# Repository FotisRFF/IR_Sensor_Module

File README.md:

# IR_Sensor_Module

An optimized, production-ready infrared sensor module designed for precision obstacle detection, edge sensing, or line tracking. This repository contains the complete PCB design files created in **KiCad**, including manufacturing panelization layouts and single-board configurations.

---

## Key Hardware Features

* **Compact Footprint:** Engineered for tight spaces with surface-mount components and clean trace routing.
* **Optimized Optics:** Integrated phototransistor and IR LED arrangement designed for reliable ambient light rejection and consistent response distances.
* **Panelization Ready:** Includes optimized panel layouts suitable for automated pick-and-place assembly and batch fabrication.

---

## Board Layouts & Visualizations

### Panel View

* **PCB Layout:**  

* **3D Rendering:**  

---

### Single Board View

* **PCB Layout:**  

* **3D Rendering:**  

---

## Repository Structure

```text
├── Kicad_Files/          # Schematic & PCB layout project files
├── Fabrication/          # Gerber files, panel assembly drawings, and BOM
└── README.md             # Project documentation

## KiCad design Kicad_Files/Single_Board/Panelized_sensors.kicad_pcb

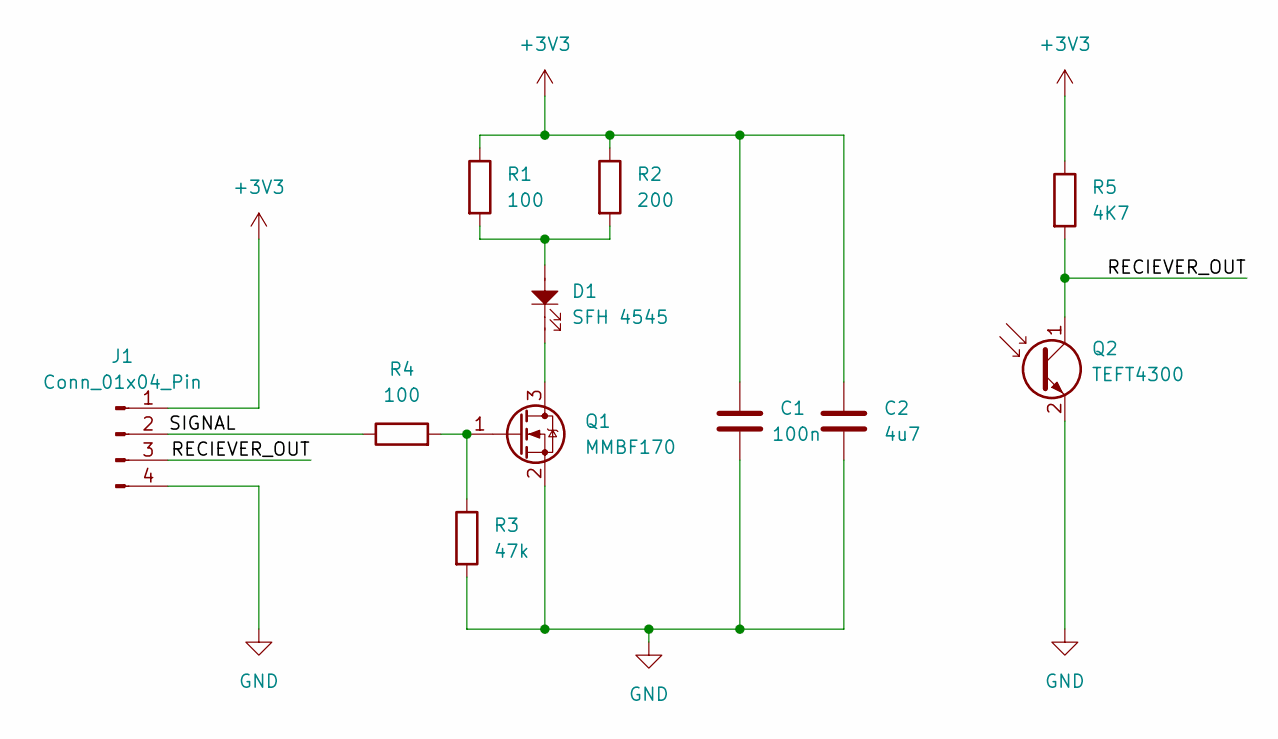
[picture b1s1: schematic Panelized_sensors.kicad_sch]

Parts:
C1: 100n; C_0402_1005Metric_Pad0.74x0.62mm_HandSolder
C2: 4u7; C_0603_1608Metric
D1: SFH 4545; LED_D5.0mm_Clear
J1: Conn_01x04_Pin; default values pad 1x4
Q1: MMBF170; SOT-23
Q2: TEFT4300; LED_D5.0mm_Clear
R1, R4: 100; R_0603_1608Metric
R2: 200; R_0603_1608Metric
R3: 47k; R_0603_1608Metric
R5: 4K7; R_0603_1608Metric

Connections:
+3V3: C1.1, C2.1, J1.1, R1.1, R2.1, R5.1
/RECIEVER_OUT: J1.3, Q2.1 (C), R5.2
/SIGNAL: J1.2, R4.1
GND: C1.2, C2.2, J1.4, Q1.2 (S), Q2.2 (E), R3.2
unnamed: D1.2, R1.2, R2.2
unnamed: D1.1, Q1.3 (D)
unnamed: Q1.1 (G), R3.1, R4.2

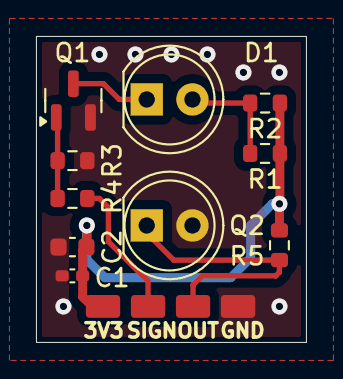
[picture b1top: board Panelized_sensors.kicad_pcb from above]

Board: 2 copper layers, 15.0 x 17.0 mm, 11 parts (0 on the bottom side), 7 nets.
